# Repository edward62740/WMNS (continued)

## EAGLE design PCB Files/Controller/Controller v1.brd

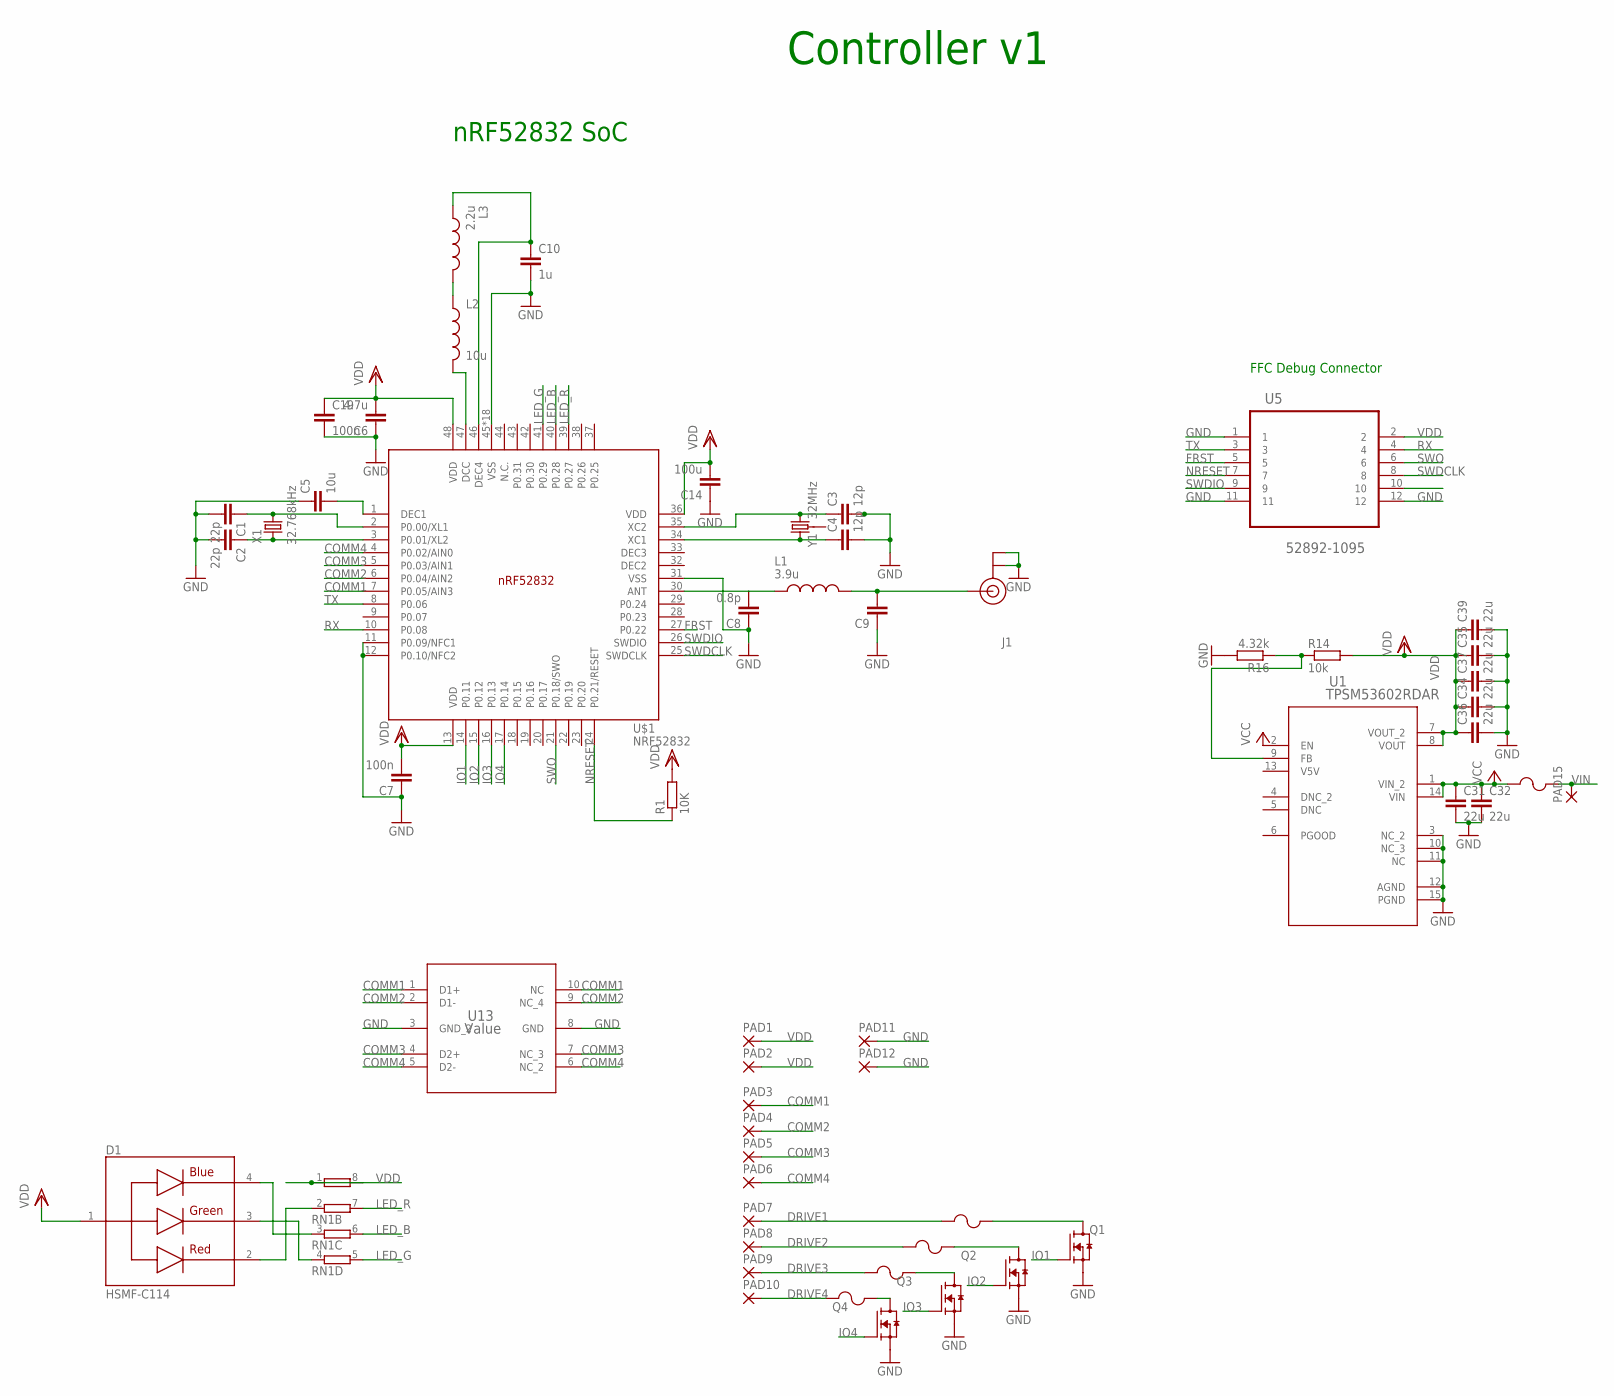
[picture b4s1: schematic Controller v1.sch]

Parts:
C1, C2: 22p; C0402
C3, C4: 12p; C0402
C5: 10u; C0402
C6: 4.7u; C0402
C7: 100n; C0603R
C8: 0.8p; C0402
C9: 1.2p; C0402
C10: 1u; C0402
C14: 100u; C0402
C19: 100n; C0402
C31, C32, C34, C35, C36, C37, C39: 22u; C0603R
D1: HSMF-C114; DIOSC160X150X35-4N
F1, F2, F3, F4, F5: 1210L050YR1210LSERIES_LTF-L; 1210LSERIES_LTF-L
J1: U.FL
L1: 3.9u; INDC0402X26N
L2: 10u; L0603
L3: 2.2u; INDC0402X26N
PAD1, PAD2, PAD3, PAD4, PAD5, PAD6, PAD7, PAD8, PAD9, PAD10, PAD11, PAD12, PAD15: 2,54/1,1
Q1, Q2, Q3, Q4: CSD16301Q2; TRANS_CSD16301Q2
R1: 10K; R0402
R14: 10k; R0402
R16: 4.32k; R0402
RN1: 4R-N0402ARV341; 4X0402ARV341
U1: TPSM53602RDAR; B3QFN15_RDA_TEX
U5: 52892-1095; MOLEX_52892-1095
U13: Value; DQA0010A
U$1: NRF52832; QFN40P600X600X90-48_N
X1: 32.768kHz; ABS07-32.768KHZ-T
Y1: 32MHz; CRYSTAL-SMD-3.2X2.5MM

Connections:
COMM1: PAD3.1, U13.1 (D1+), U13.10 (NC), U$1.7 (P0.05/AIN3)
COMM2: PAD4.1, U13.2 (D1-), U13.9 (NC_4), U$1.6 (P0.04/AIN2)
COMM3: PAD5.1, U13.4 (D2+), U13.7 (NC_3), U$1.5 (P0.03/AIN1)
COMM4: PAD6.1, U13.5 (D2-), U13.6 (NC_2), U$1.4 (P0.02/AIN0)
DRIVE1: F5.1, PAD7.1
DRIVE2: F4.1, PAD8.1
DRIVE3: F2.1, PAD9.1
DRIVE4: F3.1, PAD10.1
FRST: U5.5, U$1.27 (P0.22)
GND: C1.2, C2.2, C3.2, C4.2, C5.1, C6.1, C7.1, C8.1, C9.1, C10.2, C14.1, C19.2, C31.2, C32.2, C34.2, C35.2, C36.2, C37.2, C39.2, J1.1 (GND), J1.2 (GND), PAD11.1, PAD12.1, Q1.4 (S), Q1.7 (S), Q2.4 (S), Q2.7 (S), Q3.4 (S), Q3.7 (S), Q4.4 (S), Q4.7 (S), R16.2, U1.3 (NC_2), U1.10 (NC_3), U1.11 (NC), U1.12 (AGND), U1.15 (PGND), U5.1, U5.11, U5.12, U13.3 (GND_2), U13.8 (GND), U$1.11 (P0.09/NFC1), U$1.12 (P0.10/NFC2), U$1.31 (VSS), U$1.45 (VSS), U$1.PAD (VSS), U$1.PAD@VIA01 (VSS), U$1.PAD@VIA02 (VSS), U$1.PAD@VIA03 (VSS), U$1.PAD@VIA04 (VSS), U$1.PAD@VIA05 (VSS), U$1.PAD@VIA06 (VSS), U$1.PAD@VIA07 (VSS), U$1.PAD@VIA08 (VSS), U$1.PAD@VIA09 (VSS), U$1.PAD@VIA10 (VSS), U$1.PAD@VIA11 (VSS), U$1.PAD@VIA12 (VSS), U$1.PAD@VIA13 (VSS), U$1.PAD@VIA14 (VSS), U$1.PAD@VIA15 (VSS), U$1.PAD@VIA16 (VSS)
IO1: Q1.3 (G), U$1.14 (P0.11)
IO2: Q2.3 (G), U$1.15 (P0.12)
IO3: Q3.3 (G), U$1.16 (P0.13)
IO4: Q4.3 (G), U$1.17 (P0.14)
LED_B: RN1.6 (2), U$1.40 (P0.28)
LED_G: RN1.5 (2), U$1.41 (P0.29)
LED_R: RN1.7 (2), U$1.39 (P0.27)
unnamed: C1.1, U$1.2 (P0.00/XL1), X1.2
unnamed: C2.1, U$1.3 (P0.01/XL2), X1.1
unnamed: C3.1, U$1.35 (XC2), Y1.3 (2)
unnamed: C4.1, U$1.34 (XC1), Y1.1
unnamed: C5.2, U$1.1 (DEC1)
unnamed: C8.2, L1.1, U$1.30 (ANT)
unnamed: F2.2, Q3.1 (D), Q3.2 (D), Q3.5 (D), Q3.6 (D), Q3.8 (D)
unnamed: F3.2, Q4.1 (D), Q4.2 (D), Q4.5 (D), Q4.6 (D), Q4.8 (D)
unnamed: L2.2, U$1.47 (DCC)
unnamed: L2.1, L3.2
unnamed: C10.1, L3.1, U$1.46 (DEC4)
unnamed: D1.2, RN1.2 (1)
unnamed: D1.3, RN1.4 (1)
unnamed: D1.4, RN1.3 (1)
unnamed: F4.2, Q2.1 (D), Q2.2 (D), Q2.5 (D), Q2.6 (D), Q2.8 (D)
unnamed: F5.2, Q1.1 (D), Q1.2 (D), Q1.5 (D), Q1.6 (D), Q1.8 (D)
unnamed: R14.1, R16.1, U1.9 (FB)
NRESET: R1.1, U5.7, U$1.24 (P0.21/RESET)
RF: C9.2, J1.FEED (SIGNAL), L1.2
RX: U5.4, U$1.10 (P0.08)
SWDCLK: U5.8, U$1.25 (SWDCLK)
SWDIO: U5.9, U$1.26 (SWDIO)
SWO: U5.6, U$1.21 (P0.18/SWO)
TX: U5.3, U$1.8 (P0.06)
VCC: C31.1, C32.1, F1.1, U1.1 (VIN_2), U1.2 (EN), U1.14 (VIN)
VDD: C6.2, C7.2, C14.2, C19.1, C34.1, C35.1, C36.1, C37.1, C39.1, D1.1, PAD1.1, PAD2.1, R1.2, R14.2, RN1.1, RN1.8 (2), U1.7 (VOUT_2), U1.8 (VOUT), U5.2, U$1.13 (VDD), U$1.36 (VDD), U$1.48 (VDD)
VIN: F1.2, PAD15.1

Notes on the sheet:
nRF52832 SoC
FFC Debug Connector
Controller v1

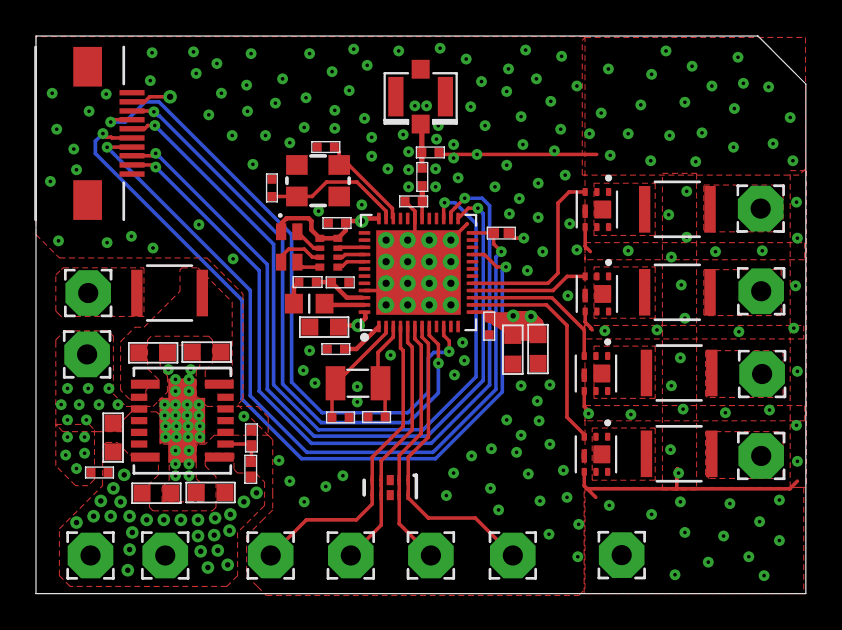
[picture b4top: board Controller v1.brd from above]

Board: 4 copper layers, 42.8 x 31.0 mm, 56 parts (0 on the bottom side), 44 nets.

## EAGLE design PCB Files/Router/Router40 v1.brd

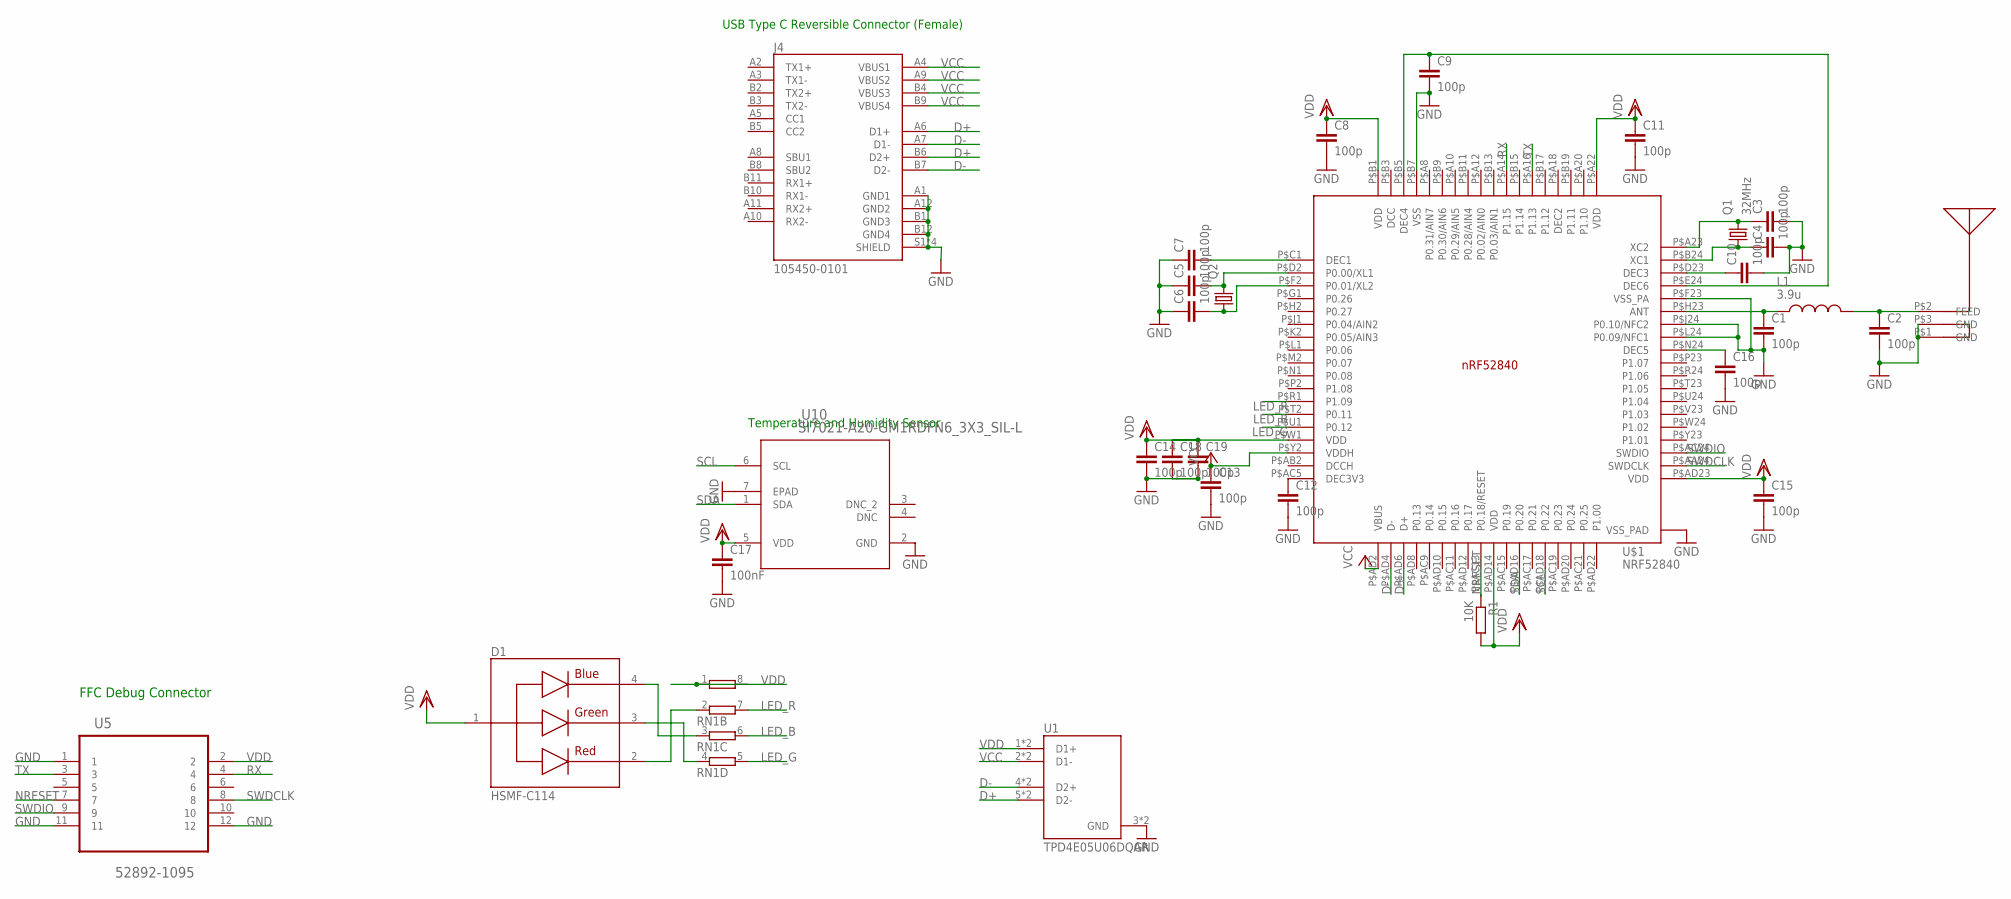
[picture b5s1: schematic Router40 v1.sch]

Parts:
C1, C2, C3, C4, C5, C6, C7, C8, C9, C10, C11, C12, C13, C14, C15, C16, C18, C19: 100p; C0402
C17: 100nF; C0402
D1: HSMF-C114; DIOSC160X150X35-4N
J4: 105450-0101; MOLEX_105450-0101
L1: 3.9u; INDC0402X26N
Q1: 32MHz; 2.0X1.6_KX-5
Q2: KX-327-RT; 2.0X1.2
R1: 10K; R0402
RN1: 4R-N0402ARV341; 4X0402ARV341
U1: TPD4E05U06DQAR; TI_TPD4E05U06DQAR
U5: 52892-1095; MOLEX_52892-1095
U10: SI7021-A20-GM1RDFN6_3X3_SIL-L; DFN6_3X3_SIL-L
U$1: NRF52840; AQFN50P700X700X85_HS-74N
U$4: CHIPANTENNAL2

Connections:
D+: J4.A6 (D1+), J4.B6 (D2+), U1.5 (D2-), U1.6 (D2-), U$1.P$AD6 (D+)
D-: J4.A7 (D1-), J4.B7 (D2-), U1.4 (D2+), U1.7 (D2+), U$1.P$AD4 (D-)
GND: C1.2, C2.2, C3.2, C4.2, C5.1, C6.1, C7.1, C8.2, C9.2, C10.2, C11.2, C12.2, C13.2, C14.2, C15.2, C16.2, C17.2, C18.2, C19.2, J4.A1 (GND1), J4.A12 (GND2), J4.B1 (GND3), J4.B12 (GND4), J4.S1 (SHIELD), J4.S2 (SHIELD), J4.S3 (SHIELD), J4.S4 (SHIELD), U1.3 (GND), U1.8 (GND), U5.1, U5.11, U5.12, U10.2 (GND), U10.7 (EPAD), U$1.P$74 (VSS_PAD), U$1.P$75 (VSS_PAD), U$1.P$76 (VSS_PAD), U$1.P$77 (VSS_PAD), U$1.P$78 (VSS_PAD), U$1.P$79 (VSS_PAD), U$1.P$80 (VSS_PAD), U$1.P$81 (VSS_PAD), U$1.P$82 (VSS_PAD), U$1.P$83 (VSS_PAD), U$1.P$84 (VSS_PAD), U$1.P$85 (VSS_PAD), U$1.P$86 (VSS_PAD), U$1.P$87 (VSS_PAD), U$1.P$88 (VSS_PAD), U$1.P$89 (VSS_PAD), U$1.P$90 (VSS_PAD), U$1.P$B7 (VSS), U$1.P$F23 (VSS_PA), U$1.P$J24 (P0.10/NFC2), U$1.P$L24 (P0.09/NFC1), U$4.P$1 (GND), U$4.P$3 (GND)
LED_B: RN1.6 (2), U$1.P$T2 (P0.11)
LED_G: RN1.5 (2), U$1.P$U1 (P0.12)
LED_R: RN1.7 (2), U$1.P$R1 (P1.09)
unnamed: C1.1, L1.1, U$1.P$H23 (ANT)
unnamed: C2.1, L1.2, U$4.P$2 (FEED)
unnamed: C3.1, Q1.3 (2), U$1.P$A23 (XC2)
unnamed: C4.1, Q1.1, U$1.P$B24 (XC1)
unnamed: C5.2, Q2.2, U$1.P$D2 (P0.00/XL1)
unnamed: C6.2, Q2.1, U$1.P$F2 (P0.01/XL2)
unnamed: C7.2, U$1.P$C1 (DEC1)
unnamed: C9.1, U$1.P$B5 (DEC4), U$1.P$E24 (DEC6)
unnamed: C10.1, U$1.P$D23 (DEC3)
unnamed: C12.1, U$1.P$AC5 (DEC3V3)
unnamed: C16.1, U$1.P$N24 (DEC5)
unnamed: D1.2, RN1.2 (1)
unnamed: D1.3, RN1.4 (1)
unnamed: D1.4, RN1.3 (1)
NRESET: R1.1, U5.7, U$1.P$AC13 (P0.18/RESET)
RX: U5.4, U$1.P$A14 (P1.15)
SCL: U10.6 (SCL), U$1.P$AD18 (P0.22)
SDA: U10.1 (SDA), U$1.P$AD16 (P0.20)
SWDCLK: U5.8, U$1.P$AA24 (SWDCLK)
SWDIO: U5.9, U$1.P$AC24 (SWDIO)
TX: U5.3, U$1.P$A16 (P1.13)
VCC: C13.1, J4.A4 (VBUS1), J4.A9 (VBUS2), J4.B4 (VBUS3), J4.B9 (VBUS4), U1.2 (D1-), U1.9 (D1-), U$1.P$AD2 (VBUS), U$1.P$Y2 (VDDH)
VDD: C8.1, C11.1, C14.1, C15.1, C17.1, C18.1, C19.1, D1.1, R1.2, RN1.1, RN1.8 (2), U1.1 (D1+), U1.10 (D1+), U5.2, U10.5 (VDD), U$1.P$A22 (VDD), U$1.P$AD14 (VDD), U$1.P$AD23 (VDD), U$1.P$B1 (VDD), U$1.P$W1 (VDD)

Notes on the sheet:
FFC Debug Connector
USB Type C Reversible Connector (Female)
Temperature and Humidity Sensor

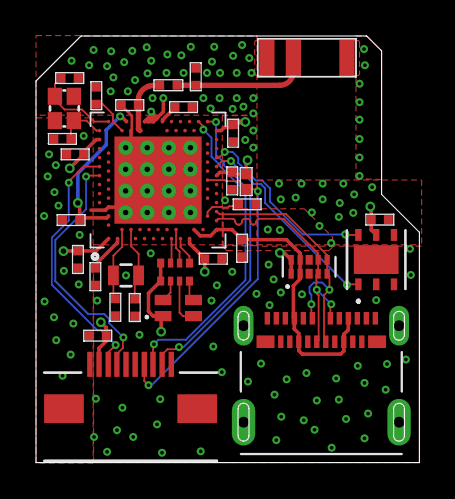
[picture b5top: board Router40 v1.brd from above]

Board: 4 copper layers, 21.3 x 23.7 mm, 31 parts (0 on the bottom side), 29 nets.

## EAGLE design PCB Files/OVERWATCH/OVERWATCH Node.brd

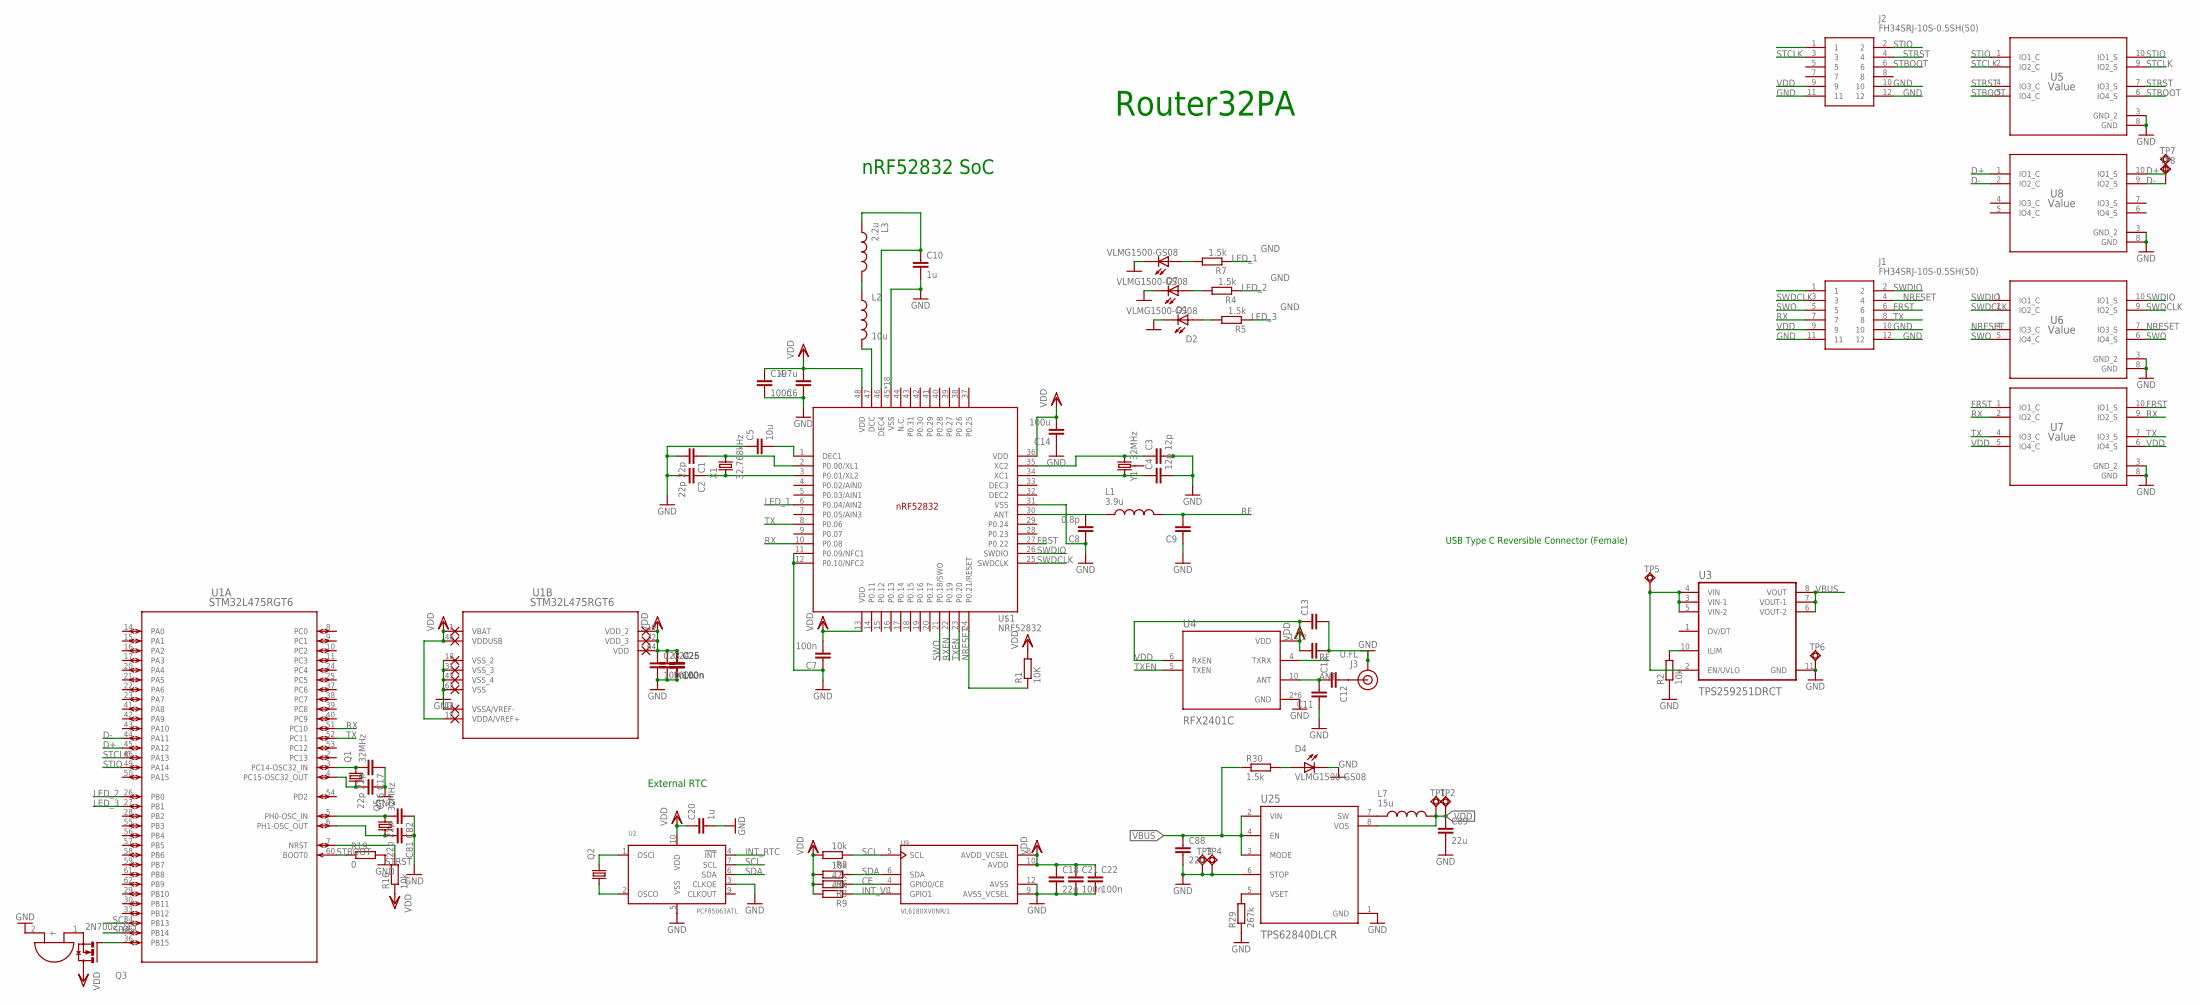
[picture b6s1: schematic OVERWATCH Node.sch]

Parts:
C1, C2, C16, C17, C81, C82: 22p; C0402
C3, C4: 12p; C0402
C5: 10u; C0402
C6: 4.7u; C0402
C7: 100n; C0603R
C8: 0.8p; C0402
C9, C11, C12, C13, C15: 1.2p; C0402
C10: 1u; C0402
C14: 100u; C0402
C18, C88, C89: 22u; C0603R
C19, C21, C22, C23, C24, C25, C26: 100n; C0402
C20: 1u; C0603R
D1, D2, D4, D7: VLMG1500-GS08; LEDC1005X35N
J1, J2: FH34SRJ-10S-0.5SH(50); FH34SRJ10S05SH50
J3: U.FL
L1: 3.9u; INDC0402X26N
L2: 10u; L0603
L3: 2.2u; INDC0402X26N
L7: 15u; INDC3225X120N
Q1, Q5: 32MHz; 2.0X1.6_KX-5
Q2: KX-327-RT; 2.0X1.2
Q3: 2N7002,215; SOT23-3
R1: 10K; R0402
R2, R3, R6, R16: 10k; R0402
R4, R5, R7, R30: 1.5k; R0402
R8, R9: 47k; R0402
R19: 0; R0402
R29: 267k; R0402
TP1, TP2, TP3, TP4, TP5, TP6, TP7, TP8: TESTPAD_TPSQTP20SQ; TESTPAD_TP20SQ
U1: STM32L475RGT6; LQFP64-10X10MM
U2: PCF85063ATL; SOT1197-1
U3: TPS259251DRCT; VREG_V62/16624-01YE
U4: RFX2401C; QFN50P300X300X60-17N
U5, U6, U7, U8: Value; DQA0010A
U9: VL6180XV0NR/1; LGA12R75P2X6_280X480X110
U25: TPS62840DLCR; SON50P200X150X100-8N
U$1: NRF52832; QFN40P600X600X90-48_N
U$2: SMD_BUZZER
X1: 32.768kHz; ABS07-32.768KHZ-T
Y1: 32MHz; CRYSTAL-SMD-3.2X2.5MM

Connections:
ANT: C11.2, C12.2, U4.10 (ANT)
CE: R8.1, U9.4 (GPIO0/CE)
D+: TP7.TP, U1.45 (PA12), U8.1 (IO1_C), U8.10 (IO1_S)
D-: TP8.TP, U1.44 (PA11), U8.2 (IO2_C), U8.9 (IO2_S)
FRST: J1.6, U7.1 (IO1_C), U7.10 (IO1_S), U$1.27 (P0.22)
GND: C1.2, C2.2, C3.2, C4.2, C5.1, C6.1, C7.1, C8.1, C9.1, C10.2, C11.1, C13.2, C14.1, C15.1, C16.1, C17.1, C18.2, C19.2, C20.2, C21.2, C22.2, C23.2, C24.2, C25.2, C26.2, C81.1, C82.1, C88.2, C89.2, D1.2, D2.2, D4.2, D7.2, J1.10, J1.11, J1.12, J2.10, J2.11, J2.12, J3.1 (GND), J3.2 (GND), R2.1, R19.2, R29.1, TP3.TP, TP4.TP, TP6.TP, U1.12 (VSSA/VREF-), U1.18 (VSS_2), U1.31 (VSS_3), U1.47 (VSS_4), U1.63 (VSS), U2.3 (CLKOE), U2.5 (VSS), U3.11 (GND), U4.2 (GND), U4.3 (GND), U4.8 (GND), U4.9 (GND), U4.11 (GND), U4.17 (GND), U5.3 (GND_2), U5.8 (GND), U6.3 (GND_2), U6.8 (GND), U7.3 (GND_2), U7.8 (GND), U8.3 (GND_2), U8.8 (GND), U9.9 (AVSS_VCSEL), U9.12 (AVSS), U25.1 (GND), U25.6 (STOP), U$1.11 (P0.09/NFC1), U$1.12 (P0.10/NFC2), U$1.31 (VSS), U$1.45 (VSS), U$1.PAD (VSS), U$1.PAD@VIA01 (VSS), U$1.PAD@VIA02 (VSS), U$1.PAD@VIA03 (VSS), U$1.PAD@VIA04 (VSS), U$1.PAD@VIA05 (VSS), U$1.PAD@VIA06 (VSS), U$1.PAD@VIA07 (VSS), U$1.PAD@VIA08 (VSS), U$1.PAD@VIA09 (VSS), U$1.PAD@VIA10 (VSS), U$1.PAD@VIA11 (VSS), U$1.PAD@VIA12 (VSS), U$1.PAD@VIA13 (VSS), U$1.PAD@VIA14 (VSS), U$1.PAD@VIA15 (VSS), U$1.PAD@VIA16 (VSS), U$2.2 (-)
INT_RTC: U2.4 (!INT!)
INT_VL: R9.1, U9.1 (GPIO1)
LED_1: R7.1, U$1.6 (P0.04/AIN2)
LED_2: R4.1, U1.26 (PB0)
LED_3: R5.1, U1.27 (PB1)
unnamed: C1.1, U$1.2 (P0.00/XL1), X1.2
unnamed: C2.1, U$1.3 (P0.01/XL2), X1.1
unnamed: C3.1, U$1.35 (XC2), Y1.3 (2)
unnamed: C4.1, U$1.34 (XC1), Y1.1
unnamed: C5.2, U$1.1 (DEC1)
unnamed: C8.2, L1.1, U$1.30 (ANT)
unnamed: D1.1, R4.2
unnamed: D2.1, R5.2
unnamed: L2.2, U$1.47 (DCC)
unnamed: L2.1, L3.2
unnamed: C10.1, L3.1, U$1.46 (DEC4)
unnamed: Q3.2 (S), U$2.1 (+)
unnamed: C16.2, Q1.1, U1.4 (PC15-OSC32_OUT)
unnamed: C12.1, J3.FEED (SIGNAL)
unnamed: C17.2, Q1.3 (2), U1.3 (PC14-OSC32_IN)
unnamed: Q2.2, U2.1 (OSCI)
unnamed: Q2.1, U2.2 (OSCO)
unnamed: D7.1, R7.2
unnamed: R2.2, U3.10 (ILIM)
unnamed: TP5.TP, U3.2 (EN/UVLO), U3.3 (VIN-1), U3.4 (VIN), U3.5 (VIN-2)
unnamed: Q3.1 (G), U1.36 (PB15)
unnamed: C81.2, Q5.1, U1.6 (PH1-OSC_OUT)
unnamed: C82.2, Q5.3 (2), U1.5 (PH0-OSC_IN)
unnamed: L7.1, U25.7 (SW)
unnamed: R29.2, U25.5 (VSET)
unnamed: D4.1, R30.2
NRESET: J1.4, R1.1, U6.4 (IO3_C), U6.7 (IO3_S), U$1.24 (P0.21/RESET)
RF: C9.2, L1.2, U4.4 (TXRX)
RX: J1.7, U1.51 (PC10), U7.2 (IO2_C), U7.9 (IO2_S), U$1.10 (P0.08)
RXEN: U$1.22 (P0.19)
SCL: R3.1, U1.34 (PB13), U2.7 (SCL), U9.5 (SCL)
SDA: R6.1, U1.35 (PB14), U2.6 (SDA), U9.6 (SDA)
STBOOT: J2.6, R19.1, U1.60 (BOOT0), U5.5 (IO4_C), U5.6 (IO4_S)
STCLK: J2.3, U1.46 (PA13), U5.2 (IO2_C), U5.9 (IO2_S)
STIO: J2.2, U1.49 (PA14), U5.1 (IO1_C), U5.10 (IO1_S)
STRST: J2.4, R16.2, U1.7 (NRST), U5.4 (IO3_C), U5.7 (IO3_S)
SWDCLK: J1.3, U6.2 (IO2_C), U6.9 (IO2_S), U$1.25 (SWDCLK)
SWDIO: J1.2, U6.1 (IO1_C), U6.10 (IO1_S), U$1.26 (SWDIO)
SWO: J1.5, U6.5 (IO4_C), U6.6 (IO4_S), U$1.21 (P0.18/SWO)
TX: J1.8, U1.52 (PC11), U7.4 (IO3_C), U7.7 (IO3_S), U$1.8 (P0.06)
TXEN: U4.5 (TXEN), U$1.23 (P0.20)
VBUS: C88.1, R30.1, U3.6 (VOUT-2), U3.7 (VOUT-1), U3.8 (VOUT), U25.2 (VIN), U25.3 (MODE), U25.4 (EN)
VDD: C6.2, C7.2, C13.1, C14.2, C15.2, C18.1, C19.1, C20.1, C21.1, C22.1, C23.1, C24.1, C25.1, C26.1, C89.1, J1.9, J2.9, L7.2, Q3.3 (D), R1.2, R3.2, R6.2, R8.2, R9.2, R16.1, TP1.TP, TP2.TP, U1.1 (VBAT), U1.13 (VDDA/VREF+), U1.19 (VDD_2), U1.32 (VDD_3), U1.48 (VDDUSB), U1.64 (VDD), U2.10 (VDD), U4.6 (RXEN), U4.14 (VDD), U4.16 (VDD), U7.5 (IO4_C), U7.6 (IO4_S), U9.8 (AVDD_VCSEL), U9.10 (AVDD), U25.8 (VOS), U$1.13 (VDD), U$1.36 (VDD), U$1.48 (VDD)

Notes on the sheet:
nRF52832 SoC
Router32PA
USB Type C Reversible Connector (Female)
External RTC

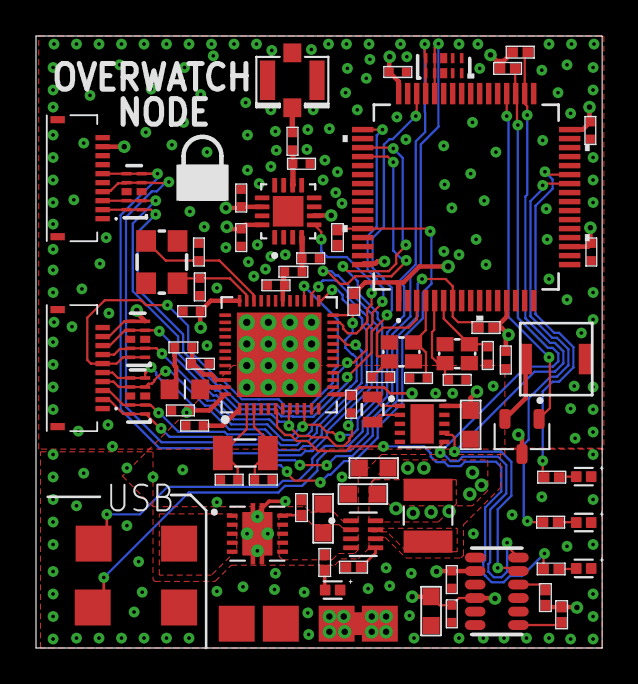
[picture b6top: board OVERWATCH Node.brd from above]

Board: 4 copper layers, 31.4 x 34.0 mm, 80 parts (0 on the bottom side), 52 nets.

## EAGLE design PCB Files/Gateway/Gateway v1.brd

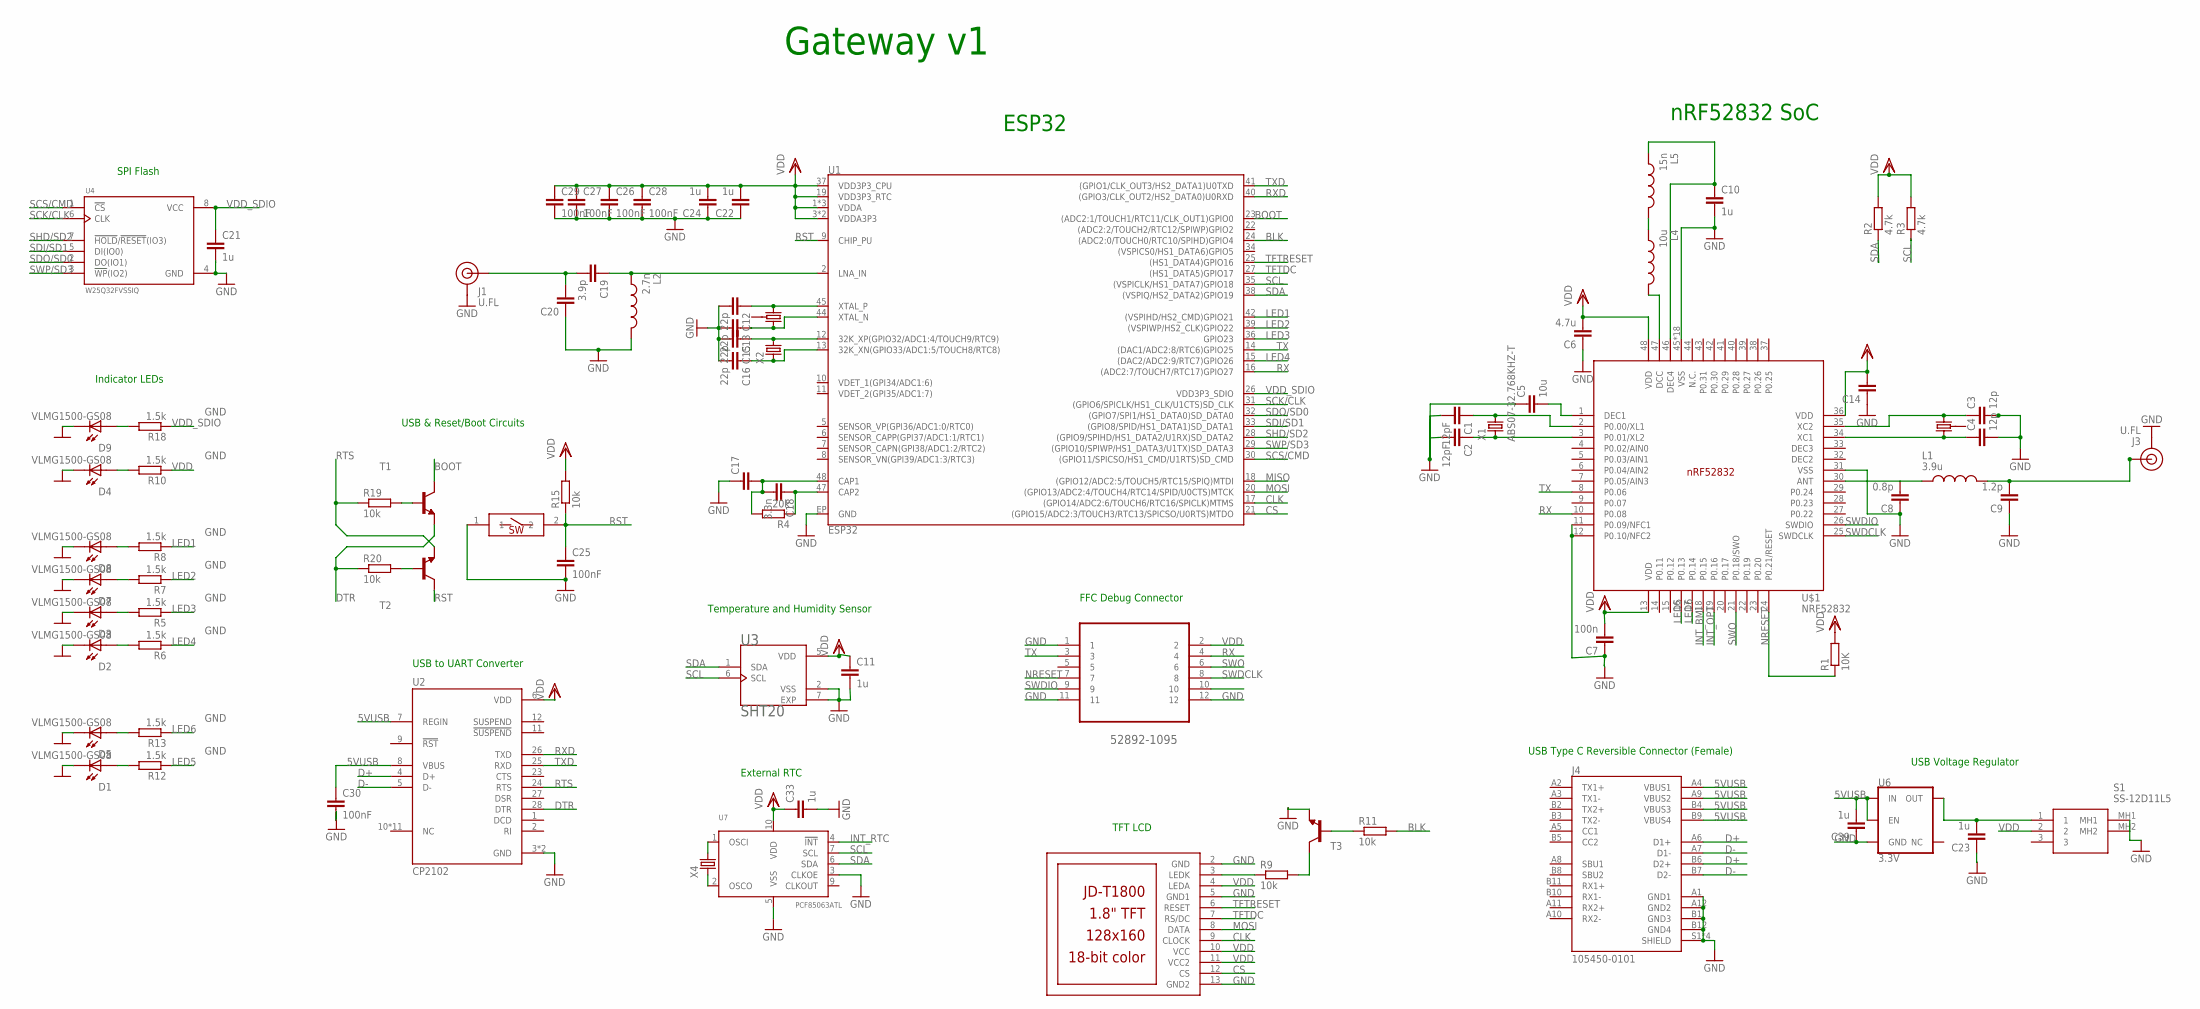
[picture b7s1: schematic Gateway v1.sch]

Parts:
C1, C2: 12pF; C0402
C3, C4: 12p; C0402
C5: 10u; C0402
C6: 4.7u; C0402
C7: 100n; C0402
C8: 0.8p; C0402
C9: 1.2p; C0402
C10, C11, C21: 1u; C0402
C12, C13, C15, C16: 22p; C0402
C14: 100u; C0402
C17: 10n; C0402
C18: 3.3n; C0402
C19: 3.9p; C0402
C20: 2.4p; C0402
C22, C23, C24, C33, C39: 1u; C0603R
C25, C26, C27, C28, C29, C30: 100nF; C0402
D1, D2, D3, D4, D5, D7, D8, D9: VLMG1500-GS08; LEDC1005X35N
J1, J3: U.FL
J4: 105450-0101; MOLEX_105450-0101
L1: 3.9u; INDC0402X26N
L2: 2.7n; INDC0402X26N
L4: 10u; INDC0402X26N
L5: 15n; INDC0402X26N
R1: 10K; R0402
R2, R3: 4.7k; R0402
R4: 20k; R0402
R5, R6, R7, R8, R10, R12, R13, R18: 1.5k; R0402
R9, R11, R15, R19, R20: 10k; R0402
RESET: SMDSWITCH; RESC4217X170
S1: SS-12D11L5; SS12D11L5
T1, T2, T3: -NPN-SOT23-BEC; SOT23-BEC
U1: ESP32; QFN48-0.4MM
U2: CP2102; QFN50P500X500X100-29N
U3: SHT20; DFN300X300X110-7N
U4: W25Q32FVSSIQ; SOIC127P790X216-8N
U5: 52892-1095; MOLEX_52892-1095
U6: 3.3V; SOT23-5
U7: PCF85063ATL; SOT1197-1
U$1: NRF52832; QFN40P600X600X90-48_N
U$2: ADAFRUIT_JD-T1800
X1, X2, X4: ABS07-32.768KHZ-T
Y1, Y2: CRYSTAL-26MHZSMD-3.2X2.5; CRYSTAL-SMD-3.2X2.5MM

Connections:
5VUSB: C30.1, C39.2, J4.A4 (VBUS1), J4.A9 (VBUS2), J4.B4 (VBUS3), J4.B9 (VBUS4), U2.7 (REGIN), U2.8 (VBUS), U6.1 (IN), U6.3 (EN)
BLK: R11.2, U1.24 ((ADC2:0/TOUCH0/RTC10/SPIHD)GPIO4)
BOOT: T1.C, U1.23 ((ADC2:1/TOUCH1/RTC11/CLK_OUT1)GPIO0)
CLK: U1.17 ((GPIO14/ADC2:6/TOUCH6/RTC16/SPICLK)MTMS), U$2.9 (CLOCK)
CS: U1.21 ((GPIO15/ADC2:3/TOUCH3/RTC13/SPICSO/U0RT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), U$2.12 (CS)
D+: J4.A6 (D1+), J4.B6 (D2+), U2.4 (D+)
D-: J4.A7 (D1-), J4.B7 (D2-), U2.5 (D-)
DTR: R20.1, T1.E, U2.28 (DTR)
GND: C1.2, C2.2, C3.2, C4.2, C5.1, C6.1, C7.1, C8.1, C9.1, C10.2, C11.2, C12.2, C13.2, C14.1, C15.2, C16.2, C17.1, C20.1, C21.2, C22.1, C23.1, C24.1, C25.2, C26.2, C27.2, C28.2, C29.2, C30.2, C33.2, C39.1, D1.2, D2.2, D3.2, D4.2, D5.2, D7.2, D8.2, D9.2, J1.1 (GND), J1.2 (GND), J3.1 (GND), J3.2 (GND), J4.A1 (GND1), J4.A12 (GND2), J4.B1 (GND3), J4.B12 (GND4), J4.S1 (SHIELD), J4.S2 (SHIELD), J4.S3 (SHIELD), J4.S4 (SHIELD), L2.2, RESET.1, S1.MH1, S1.MH2, T3.E, U1.EP (GND), U2.3 (GND), U2.29 (GND), U3.2 (VSS), U3.7 (EXP), U4.4 (GND), U5.1, U5.11, U5.12, U6.2 (GND), U7.3 (CLKOE), U7.5 (VSS), U$1.11 (P0.09/NFC1), U$1.12 (P0.10/NFC2), U$1.31 (VSS), U$1.45 (VSS), U$1.PAD (VSS), U$1.PAD@VIA01 (VSS), U$1.PAD@VIA02 (VSS), U$1.PAD@VIA03 (VSS), U$1.PAD@VIA04 (VSS), U$1.PAD@VIA05 (VSS), U$1.PAD@VIA06 (VSS), U$1.PAD@VIA07 (VSS), U$1.PAD@VIA08 (VSS), U$1.PAD@VIA09 (VSS), U$1.PAD@VIA10 (VSS), U$1.PAD@VIA11 (VSS), U$1.PAD@VIA12 (VSS), U$1.PAD@VIA13 (VSS), U$1.PAD@VIA14 (VSS), U$1.PAD@VIA15 (VSS), U$1.PAD@VIA16 (VSS), U$2.2 (GND), U$2.5 (GND1), U$2.13 (GND2)
INT_BMI: U$1.18 (P0.15)
INT_OPT: U$1.19 (P0.16)
INT_RTC: U7.4 (!INT!)
LED1: R8.1, U1.42 ((VSPIHD/HS2_CMD)GPIO21)
LED2: R7.1, U1.39 ((VSPIWP/HS2_CLK)GPIO22)
LED3: R5.1, U1.36 (GPIO23)
LED4: R6.1, U1.15 ((DAC2/ADC2:9/RTC7)GPIO26)
LED5: R12.1, U$1.16 (P0.13)
LED6: R13.1, U$1.17 (P0.14)
MISO: U1.18 ((GPIO12/ADC2:5/TOUCH5/RTC15/SPIQ)MTDI)
MOSI: U1.20 ((GPIO13/ADC2:4/TOUCH4/RTC14/SPID/U0CTS)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), U$2.8 (DATA)
unnamed: C1.1, U$1.2 (P0.00/XL1), X1.2
unnamed: C2.1, U$1.3 (P0.01/XL2), X1.1
unnamed: C3.1, U$1.35 (XC2), Y1.3 (2)
unnamed: C4.1, U$1.34 (XC1), Y1.1
unnamed: C5.2, U$1.1 (DEC1)
unnamed: C8.2, L1.1, U$1.30 (ANT)
unnamed: C13.1, U1.44 (XTAL_N), Y2.3 (2)
unnamed: C12.1, U1.45 (XTAL_P), Y2.1
unnamed: L4.2, U$1.47 (DCC)
unnamed: L4.1, L5.2
unnamed: C10.1, L5.1, U$1.46 (DEC4)
unnamed: C15.1, U1.12 (32K_XP(GPIO32/ADC1:4/TOUCH9/RTC9)), X2.2
unnamed: C16.1, U1.13 (32K_XN(GPIO33/ADC1:5/TOUCH8/RTC8)), X2.1
unnamed: C18.1, R4.1, U1.47 (CAP2)
unnamed: R19.2, T1.B
unnamed: C17.2, C18.2, R4.2, U1.48 (CAP1)
unnamed: R20.2, T2.B
unnamed: D3.1, R5.2
unnamed: D7.1, R7.2
unnamed: D8.1, R8.2
unnamed: C19.1, L2.1, U1.2 (LNA_IN)
unnamed: D2.1, R6.2
unnamed: D4.1, R10.2
unnamed: D1.1, R12.2
unnamed: D5.1, R13.2
unnamed: C19.2, C20.2, J1.FEED (SIGNAL)
unnamed: R9.1, U$2.3 (LEDK)
unnamed: C23.2, S1.1, U6.5 (OUT)
unnamed: D9.1, R18.2
unnamed: U7.1 (OSCI), X4.2
unnamed: U7.2 (OSCO), X4.1
unnamed: R11.1, T3.B
unnamed: R9.2, T3.C
NRESET: R1.1, U5.7, U$1.24 (P0.21/RESET)
RFP1: C9.2, J3.FEED (SIGNAL), L1.2
RST: C25.1, R15.1, RESET.2, T2.C, U1.9 (CHIP_PU)
RTS: R19.1, T2.E, U2.24 (RTS)
RX: U1.16 ((ADC2:7/TOUCH7/RTC17)GPIO27), U5.4, U$1.10 (P0.08)
RXD: U1.40 ((GPIO3/CLK_OUT2/HS2_DATA0)U0RXD), U2.26 (TXD)
SCK/CLK: U1.31 ((GPIO6/SPICLK/HS1_CLK/U1CTS)SD_CLK), U4.6 (CLK)
SCL: R3.1, U1.35 ((VSPICLK/HS1_DATA7)GPIO18), U3.6 (SCL), U7.7 (SCL)
SCS/CMD: U1.30 ((GPIO11/SPICSO/HS1_CMD/U1RTS)SD_CMD), U4.1 (!CS)
SDA: R2.1, U1.38 ((VSPIQ/HS2_DATA2)GPIO19), U3.1 (SDA), U7.6 (SDA)
SDI/SD1: U1.33 ((GPIO8/SPID/HS1_DATA1)SD_DATA1), U4.5 (DI(IO0))
SDO/SD0: U1.32 ((GPIO7/SPI1/HS1_DATA0)SD_DATA0), U4.2 (DO(IO1))
SHD/SD2: U1.28 ((GPIO9/SPIHD/HS1_DATA2/U1RX)SD_DATA2), U4.7 (!HOLD!/!RESET!(IO3))
SWDCLK: U5.8, U$1.25 (SWDCLK)
SWDIO: U5.9, U$1.26 (SWDIO)
SWO: U5.6, U$1.21 (P0.18/SWO)
SWP/SD3: U1.29 ((GPIO10/SPIWP/HS1_DATA3/U1TX)SD_DATA3), U4.3 (!WP!(IO2))
TFTDC: U1.27 ((HS1_DATA5)GPIO17), U$2.7 (RS/DC)
TFTRESET: U1.25 ((HS1_DATA4)GPIO16), U$2.6 (RESET)
TX: U1.14 ((DAC1/ADC2:8/RTC6)GPIO25), U5.3, U$1.8 (P0.06)
TXD: U1.41 ((GPIO1/CLK_OUT3/HS2_DATA1)U0TXD), U2.25 (RXD)
VDD: C6.2, C7.2, C11.1, C14.2, C22.2, C24.2, C26.1, C27.1, C28.1, C29.1, C33.1, R1.2, R2.2, R3.2, R10.1, R15.2, S1.2, U1.1 (VDDA), U1.3 (VDDA3P3), U1.4 (VDDA3P3), U1.19 (VDD3P3_RTC), U1.37 (VDD3P3_CPU), U1.43 (VDDA), U1.46 (VDDA), U2.6 (VDD), U3.5 (VDD), U5.2, U7.10 (VDD), U$1.13 (VDD), U$1.36 (VDD), U$1.48 (VDD), U$2.4 (LEDA), U$2.10 (VCC), U$2.11 (VCC2)
VDD_SDIO: C21.1, R18.1, U1.26 (VDD3P3_SDIO), U4.8 (VCC)

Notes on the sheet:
USB & Reset/Boot Circuits
Indicator LEDs
SPI Flash
USB to UART Converter
External RTC
Temperature and Humidity Sensor
FFC Debug Connector
TFT LCD
USB Type C Reversible Connector (Female)
USB Voltage Regulator
nRF52832 SoC
ESP32
Gateway v1

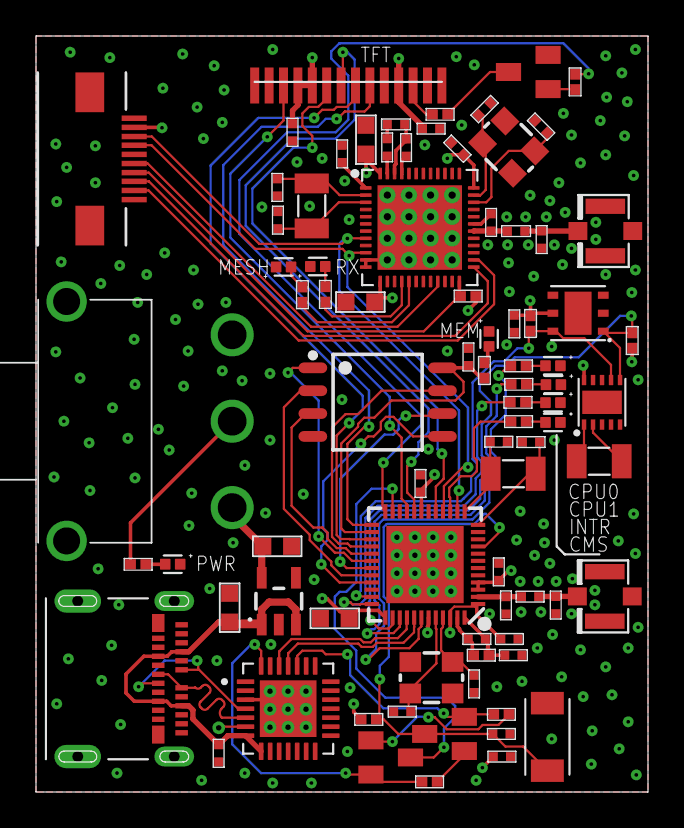
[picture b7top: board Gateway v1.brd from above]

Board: 4 copper layers, 34.0 x 42.0 mm, 83 parts (0 on the bottom side), 72 nets.

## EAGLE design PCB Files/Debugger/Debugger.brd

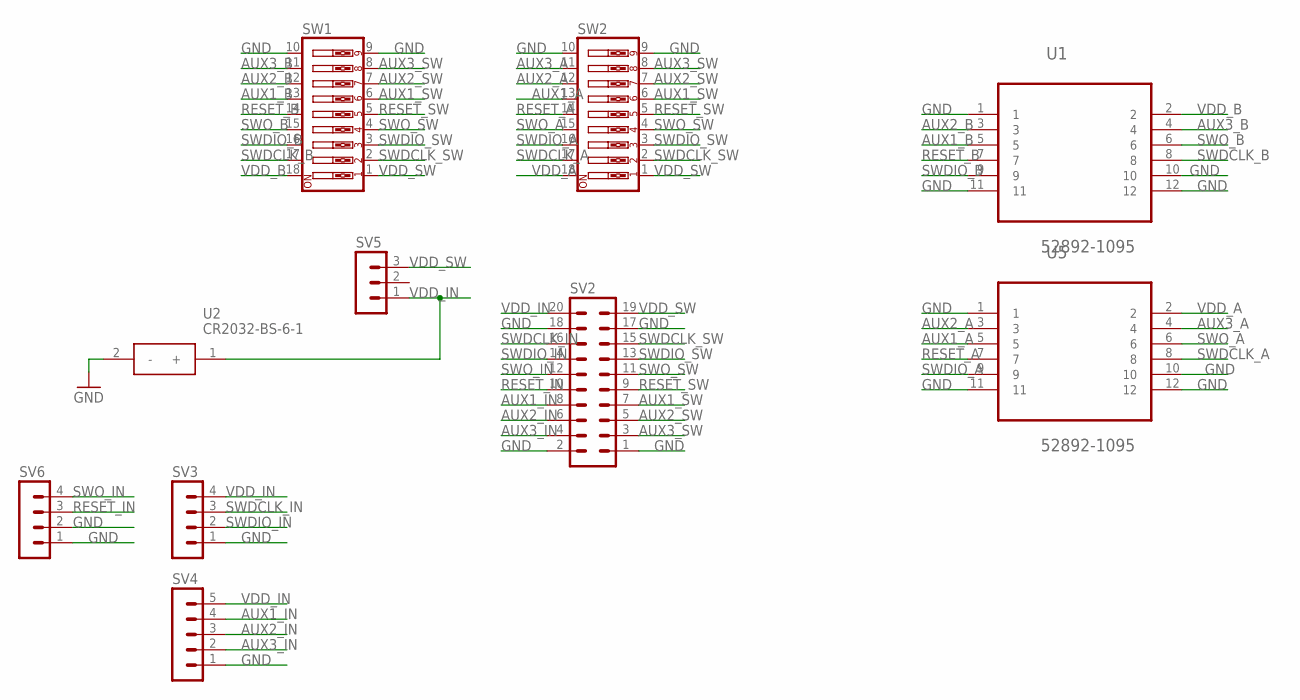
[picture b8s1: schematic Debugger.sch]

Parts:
SV2: MA10-2
SV3, SV6: MA04-1
SV4: MA05-1
SV5: MA03-1
SW1, SW2: SW_DIP-9; EDG-09
U1, U5: 52892-1095; MOLEX_52892-1095
U2: CR2032-BS-6-1; CR2032BS61

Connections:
AUX1_A: SW2.13, U5.5
AUX1_B: SW1.13, U1.5
AUX1_IN: SV2.8, SV4.4
AUX1_SW: SV2.7, SW1.6, SW2.6
AUX2_A: SW2.12, U5.3
AUX2_B: SW1.12, U1.3
AUX2_IN: SV2.6, SV4.3
AUX2_SW: SV2.5, SW1.7, SW2.7
AUX3_A: SW2.11, U5.4
AUX3_B: SW1.11, U1.4
AUX3_IN: SV2.4, SV4.2
AUX3_SW: SV2.3, SW1.8, SW2.8
GND: SV2.1, SV2.2, SV2.17, SV2.18, SV3.1, SV4.1, SV6.1, SV6.2, SW1.9, SW1.10, SW2.9, SW2.10, U1.1, U1.10, U1.11, U1.12, U2.2 (-), U5.1, U5.10, U5.11, U5.12
RESET_A: SW2.14, U5.7
RESET_B: SW1.14, U1.7
RESET_IN: SV2.10, SV6.3
RESET_SW: SV2.9, SW1.5, SW2.5
SWDCLK_A: SW2.17, U5.8
SWDCLK_B: SW1.17, U1.8
SWDCLK_IN: SV2.16, SV3.3
SWDCLK_SW: SV2.15, SW1.2, SW2.2
SWDIO_A: SW2.16, U5.9
SWDIO_B: SW1.16, U1.9
SWDIO_IN: SV2.14, SV3.2
SWDIO_SW: SV2.13, SW1.3, SW2.3
SWO_A: SW2.15, U5.6
SWO_B: SW1.15, U1.6
SWO_IN: SV2.12, SV6.4
SWO_SW: SV2.11, SW1.4, SW2.4
VDD_A: SW2.18, U5.2
VDD_B: SW1.18, U1.2
VDD_IN: SV2.20, SV3.4, SV4.5, SV5.1, U2.1 (+)
VDD_SW: SV2.19, SV5.3, SW1.1, SW2.1
